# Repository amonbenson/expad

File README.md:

# expad - Expression Adapter

A four-jack USB MIDI adapter for expression and sustain pedals, built on a Raspberry Pi Pico 2 W.
It works out what is plugged into each jack - whichever contact a pedal's wiper is on, and whether
it is a potentiometer, a switch or a two-wire rheostat - and sends every pedal's position as a MIDI
control change, ~190 times per second. A WiFi access point serves a web interface for watching the
jacks and changing the settings live.

## Hardware

The PCB is the KiCad project in [hardware/](hardware/). Each jack's tip, ring and sleeve (plus the
tip's switch contact, for plug detection) can be switched to a shared 1 kΩ pull-up to the 2.5 V
reference or a 1 kΩ pull-down, and is read back by one of two AD7718 24-bit ADCs. The four
WS2812B LEDs below the jacks glow a dim white while a plug is in but no known pedal is behind it.
A recognised pedal is announced for a second in its own color - purple for an expression pedal,
lime for a footswitch, yellow for a rheostat - after which the LED shows the value it sends, from
dark red at 0 through red, orange and yellow to white at 127. They run off a linear regulator, so
the firmware caps them at ~4% brightness.

## Supported pedals

| Pedal | Cable | Shown as | Value |
|---|---|---|---|
| Expression pedal (potentiometer), wiper on tip or ring | stereo (TRS) | Tracking | wiper position, counting up away from the sleeve |
| Sustain pedal / footswitch | mono (TS) or stereo | Switch | 100% closed, 0% open |
| Two-wire (rheostat) expression pedal | mono or stereo | Rheostat | resistance against the nearest standard value (10k, 25k, 50k ...) |
| Anything else (dual footswitches, other wirings) | | Other pedal | none |

Pedals are recognised within ~0.1 s of being plugged in, and unplugging is noticed just as fast.

- A normally-closed sustain pedal, or an expression pedal wired the other way round, needs
  **Invert**.
- A rheostat pedal on a mono cable first reads as a potentiometer at rest, until its resistance has
  changed by a fifth.
- A potentiometer pedal needs a stereo cable: with a mono one, most pedals short their ring to the
  sleeve, which leaves a resistance that rises and falls again over the travel.
- A mono cable with nothing at the other end reads as a released switch.

## Using it

1. Plug the Pico into a computer over USB. It shows up as a USB MIDI device; by default the
   first two jacks send CC 11 (Expression) and the last two CC 1 (Modulation), all on MIDI
   channel 1.
2. Join the WiFi network **Expression Adapter** (password: the one it was built with, see below).
   Phones, tablets and computers open the interface by themselves as the network's sign-in page;
   otherwise open http://192.168.4.1.
3. Per jack, set the MIDI channel and controller, **Invert**, and the **Range**: move the pedal to
   one end and press **Min**, to the other and press **Max**, so its travel covers the full MIDI
   range. **Drive** bends the response against a pedal's nonlinear track: centered is linear,
   turning it right makes the value rise early in the travel, left late (double-click resets it).
   **Wiper** only matters for pedals whose wiper is on the ring or sleeve and that rest on an
   end stop when plugged in; **Auto** handles the common wirings. The LED slider sets the
   brightness.

The topology panel on the right draws the selected jack's measured network.

## Setup

Needs Rust, Node.js (see `engines` in [web/package.json](web/package.json)) for the web interface,
and a debug probe (e.g. a Raspberry Pi Debug Probe) on the Pico's SWD pins.

```bash
rustup target add thumbv8m.main-none-eabihf
cargo install probe-rs-tools --locked
cp .env.example .env   # then set EXPAD_WIFI_PASSWORD (8-63 characters)
```

## Building and flashing

```bash
cargo run --bin expression_controller   # build, flash and show the log
cargo run --bin expression_controller --features no-wifi   # the same with the radio off
cargo build --no-default-features       # without the web interface (no Node.js needed)
```

The other programs in [src/bin/](src/bin/) test parts of the board:

| Program | What it does |
|---|---|
| `detect_pin_mapping` | checks every contact's switches and ADC input against the wiring table (unplug all jacks) |
| `capture` | holds every contact in one state and logs every ADC input, for noise measurements |
| `adc_characterization` | compares ADC filter rates and SPI settings on a pedal in jack 1 |
| `potentiometer` | reads a pedal in jack 1 and shows its position on the LEDs |
| `rainbow` | LED strip test |
| `midi_loopback` | echoes every USB MIDI message back to the host |
| `web_interface` | the web interface with made-up data |

## Development

```bash
cargo test -p expad-topology --target x86_64-pc-windows-msvc   # solver tests, on your host triple
cargo fmt
cargo clippy --all-features
cd web && npm run dev:mock   # web interface against a simulated device, no hardware needed
```

[AGENTS.md](AGENTS.md) describes the repository in detail, and
[docs/fast-tracking.md](docs/fast-tracking.md) the measurements and design behind the pedal
detection.

## General TODOs
- missing standard trait implementations for all types (Debug, Default, Clone, Copy, PartialEq, Eq, etc.)
- missing with_field builder methods for all config structs
- thiserror (nostd) or similar better error handling

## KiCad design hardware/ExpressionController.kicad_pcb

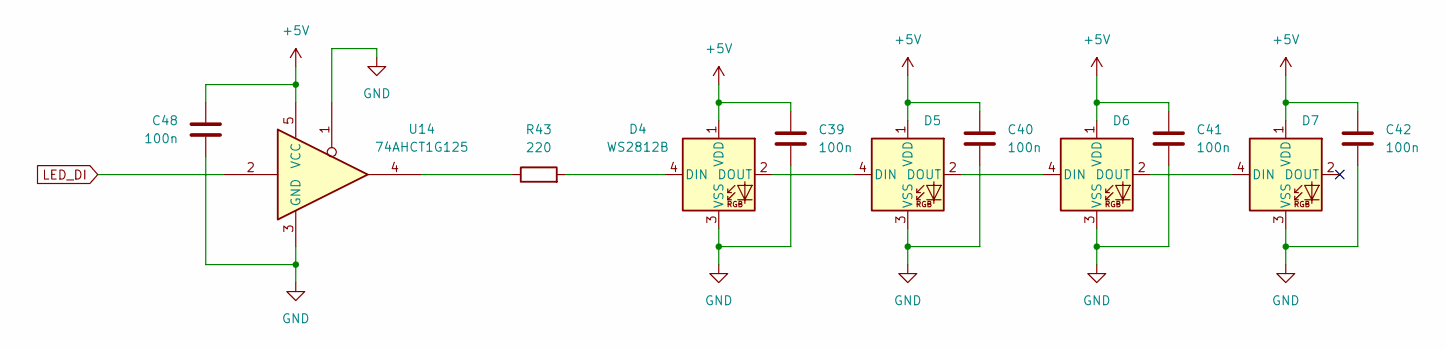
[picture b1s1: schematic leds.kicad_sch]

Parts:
C39, C40, C41, C42, C48: 100n; C_0805_2012Metric; Part Source Uni
D4, D5, D6, D7: WS2812B; LED_WS2812B_PLCC4_5.0x5.0mm_P3.2mm; Part Source Mouser; Mouser No 485-1655
R43: 220; R_0805_2012Metric; Part Source Uni
U14: 74AHCT1G125; SOT-353_SC-70-5; Part Source Mouser; Mouser No 595-74AHCT1G125DCKRG

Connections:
+5V: C39.1, C40.1, C41.1, C42.1, C48.1, D4.1 (VDD), D5.1 (VDD), D6.1 (VDD), D7.1 (VDD), U14.5 (VCC); also elsewhere on the board
GND: C39.2, C40.2, C41.2, C42.2, C48.2, D4.3 (VSS), D5.3 (VSS), D6.3 (VSS), D7.3 (VSS), U14.1, U14.3 (GND); also elsewhere on the board
LED_DI: U14.2; also elsewhere on the board
unnamed: D4.4 (DIN), R43.2
unnamed: D4.2 (DOUT), D5.4 (DIN)
unnamed: D5.2 (DOUT), D6.4 (DIN)
unnamed: D6.2 (DOUT), D7.4 (DIN)
unnamed: R43.1, U14.4

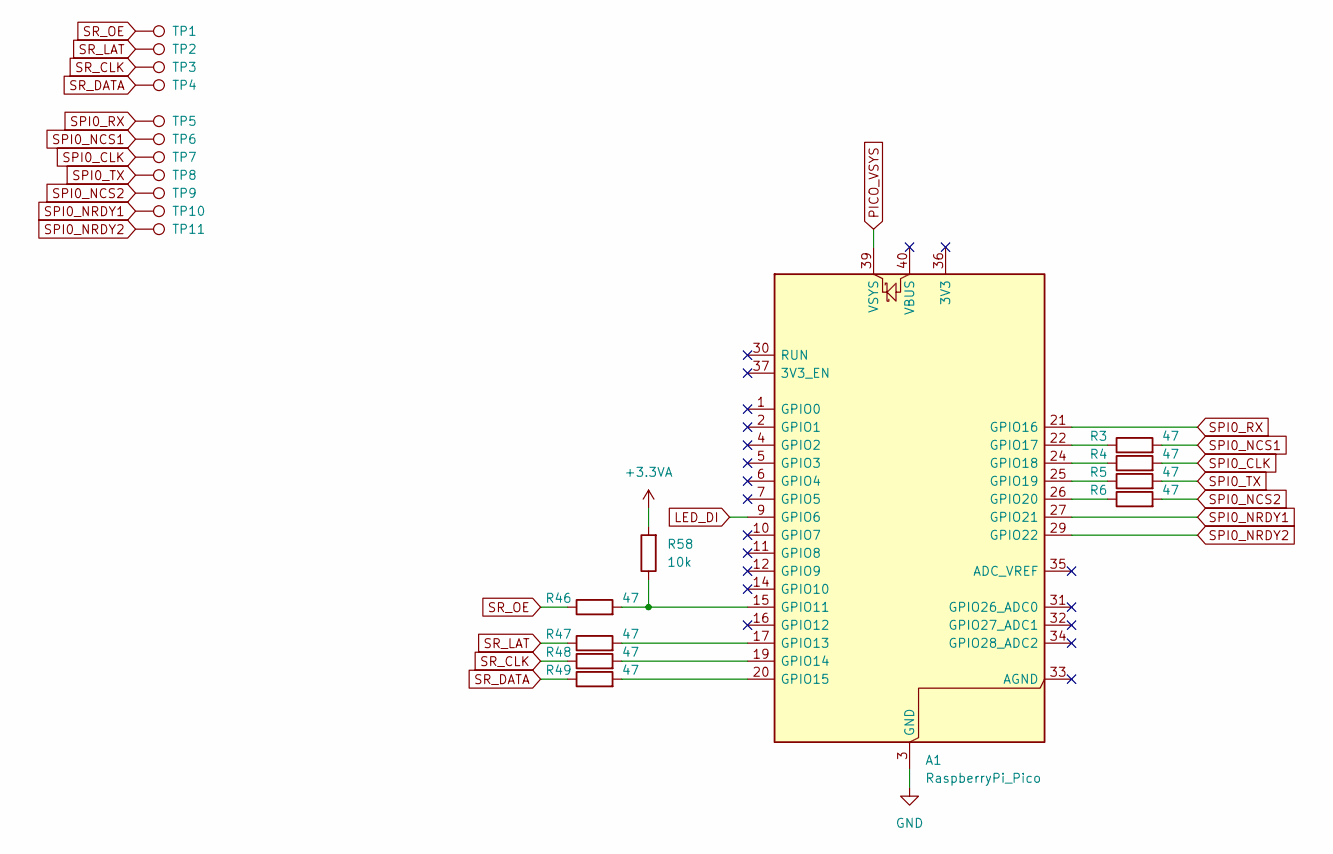
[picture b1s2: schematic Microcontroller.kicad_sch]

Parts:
A1: RaspberryPi_Pico; Pico_2W_with_Header; Part Source Uni
R3, R4, R5, R6, R46, R47, R48, R49: 47; R_0805_2012Metric; Part Source Uni
R58: 10k; R_0805_2012Metric; Part Source Uni
TP1, TP2, TP3, TP4, TP5, TP6, TP7, TP8, TP9, TP10, TP11: TestPoint; TestPoint_THTPad_D1.5mm_Drill0.7mm

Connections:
+3.3VA: R58.2; also elsewhere on the board
GND: A1.3 (GND), A1.8 (GND), A1.13 (GND), A1.18 (GND), A1.23 (GND), A1.28 (GND), A1.38 (GND); also elsewhere on the board
LED_DI: A1.9 (GPIO6); also elsewhere on the board
unnamed: A1.15 (GPIO11), R46.2, R58.1
unnamed: A1.17 (GPIO13), R47.2
unnamed: A1.19 (GPIO14), R48.2
unnamed: A1.20 (GPIO15), R49.2
unnamed: A1.22 (GPIO17), R3.1
unnamed: A1.24 (GPIO18), R4.1
unnamed: A1.25 (GPIO19), R5.1
unnamed: A1.26 (GPIO20), R6.1
PICO_VSYS: A1.39 (VSYS); also elsewhere on the board
SPI0_CLK: R4.2, TP7.1 (1_1); also elsewhere on the board
SPI0_NCS1: R3.2, TP6.1 (1_1); also elsewhere on the board
SPI0_NCS2: R6.2, TP9.1 (1_1); also elsewhere on the board
SPI0_NRDY1: A1.27 (GPIO21), TP10.1 (1_1); also elsewhere on the board
SPI0_NRDY2: A1.29 (GPIO22), TP11.1 (1_1); also elsewhere on the board
SPI0_RX: A1.21 (GPIO16), TP5.1 (1_1); also elsewhere on the board
SPI0_TX: R5.2, TP8.1 (1_1); also elsewhere on the board
SR_CLK: R48.1, TP3.1 (1_1); also elsewhere on the board
SR_DATA: R49.1, TP4.1 (1_1); also elsewhere on the board
SR_LAT: R47.1, TP2.1 (1_1); also elsewhere on the board
SR_OE: R46.1, TP1.1 (1_1); also elsewhere on the board

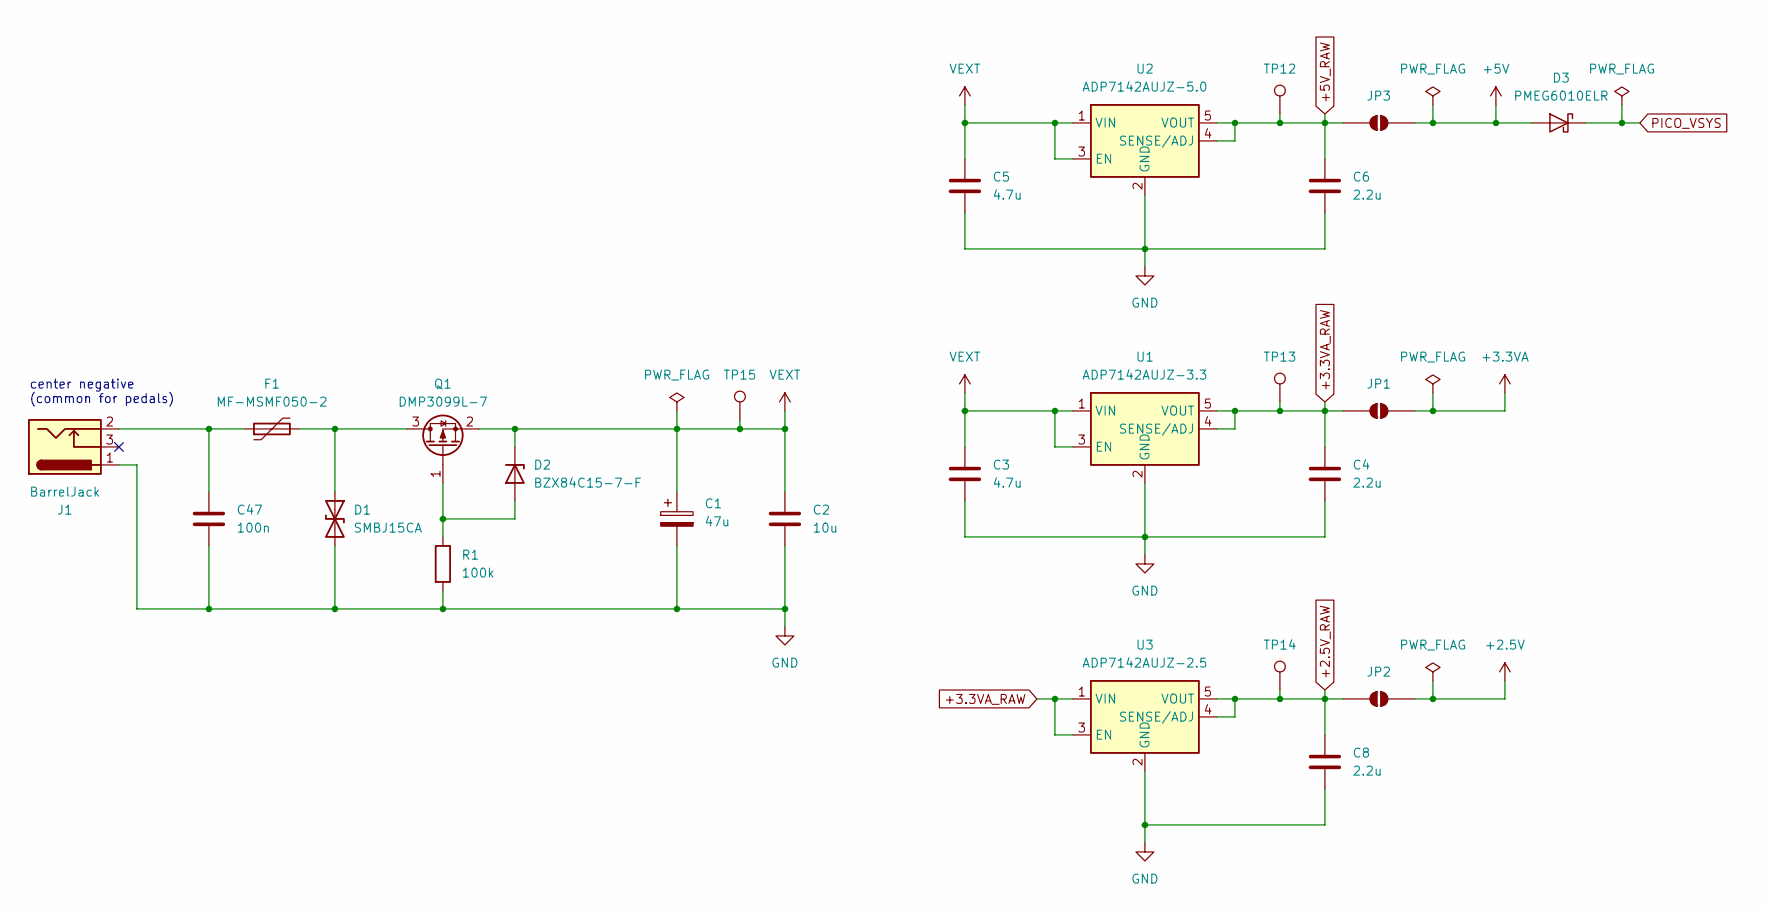
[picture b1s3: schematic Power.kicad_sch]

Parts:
C1: 47u; CP_Elec_6.3x5.8; Part Source Mouser; Mouser No 667-EEH-ZC1E470P
C2: 10u; C_0805_2012Metric; Part Source Uni
C3, C5: 4.7u; C_0805_2012Metric; Part Source Uni
C4, C6, C8: 2.2u; C_0805_2012Metric; Part Source Uni
C47: 100n; C_0805_2012Metric; Part Source Uni
D1: SMBJ15CA; D_SMB; Part Source Mouser; Mouser No 947-SMBJ15CA
D2: BZX84C15-7-F; SOT-23; Part Source Mouser; Mouser No 621-BZX84C15-F
D3: PMEG6010ELR; Nexperia_CFP3_SOD-123W; Part Source Mouser; Mouser No 771-PMEG6010ELRX
F1: MF-MSMF050-2; Fuse_1812_4532Metric; Part Source Mouser; Mouser No 652-MF-MSMF050-2
J1: BarrelJack; BarrelJack_CUI_PJ-102AH_Horizontal; Part Source Mouser; Mouser No 490-PJ-102AH
JP1, JP2, JP3: SolderJumper_2_Open; SolderJumper-2_P1.3mm_Open_RoundedPad1.0x1.5mm
Q1: DMP3099L-7; SOT-23; Part Source Mouser; Mouser No 621-DMP3099L-7
R1: 100k; R_0805_2012Metric; Part Source Uni
TP12, TP13, TP14, TP15: TestPoint; TestPoint_THTPad_D1.5mm_Drill0.7mm
U1: ADP7142AUJZ-3.3; TSOT-23-5; Part Source Mouser; Mouser No 584-ADP7142AUJZ3.3R7
U2: ADP7142AUJZ-5.0; TSOT-23-5; Part Source Mouser; Mouser No 584-ADP7142WAUJZ-50R
U3: ADP7142AUJZ-2.5; TSOT-23-5; Part Source Mouser; Mouser No 584-ADP7142AUJZ2.5R7

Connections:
+2.5V: JP2.2 (B); also elsewhere on the board
+2.5V_RAW: C8.1, JP2.1 (A), TP14.1 (1_1), U3.4 (SENSE/ADJ), U3.5 (VOUT)
+3.3VA: JP1.2 (B); also elsewhere on the board
+3.3VA_RAW: C4.1, JP1.1 (A), TP13.1 (1_1), U1.4 (SENSE/ADJ), U1.5 (VOUT), U3.1 (VIN), U3.3 (EN)
+5V: D3.2 (A), JP3.2 (B); also elsewhere on the board
+5V_RAW: C6.1, JP3.1 (A), TP12.1 (1_1), U2.4 (SENSE/ADJ), U2.5 (VOUT)
GND: C1.2, C2.2, C3.2, C4.2, C5.2, C6.2, C8.2, C47.2, D1.2 (A2), J1.1, R1.2, U1.2 (GND), U2.2 (GND), U3.2 (GND); also elsewhere on the board
unnamed: C47.1, F1.1, J1.2
unnamed: D1.1 (A1), F1.2, Q1.3 (D)
unnamed: D2.1 (A), Q1.1 (G), R1.1
PICO_VSYS: D3.1 (K); also elsewhere on the board
VEXT: C1.1, C2.1, C3.1, C5.1, D2.3 (K), Q1.2 (S), TP15.1 (1_1), U1.1 (VIN), U1.3 (EN), U2.1 (VIN), U2.3 (EN)

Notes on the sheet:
center negative (common for pedals)

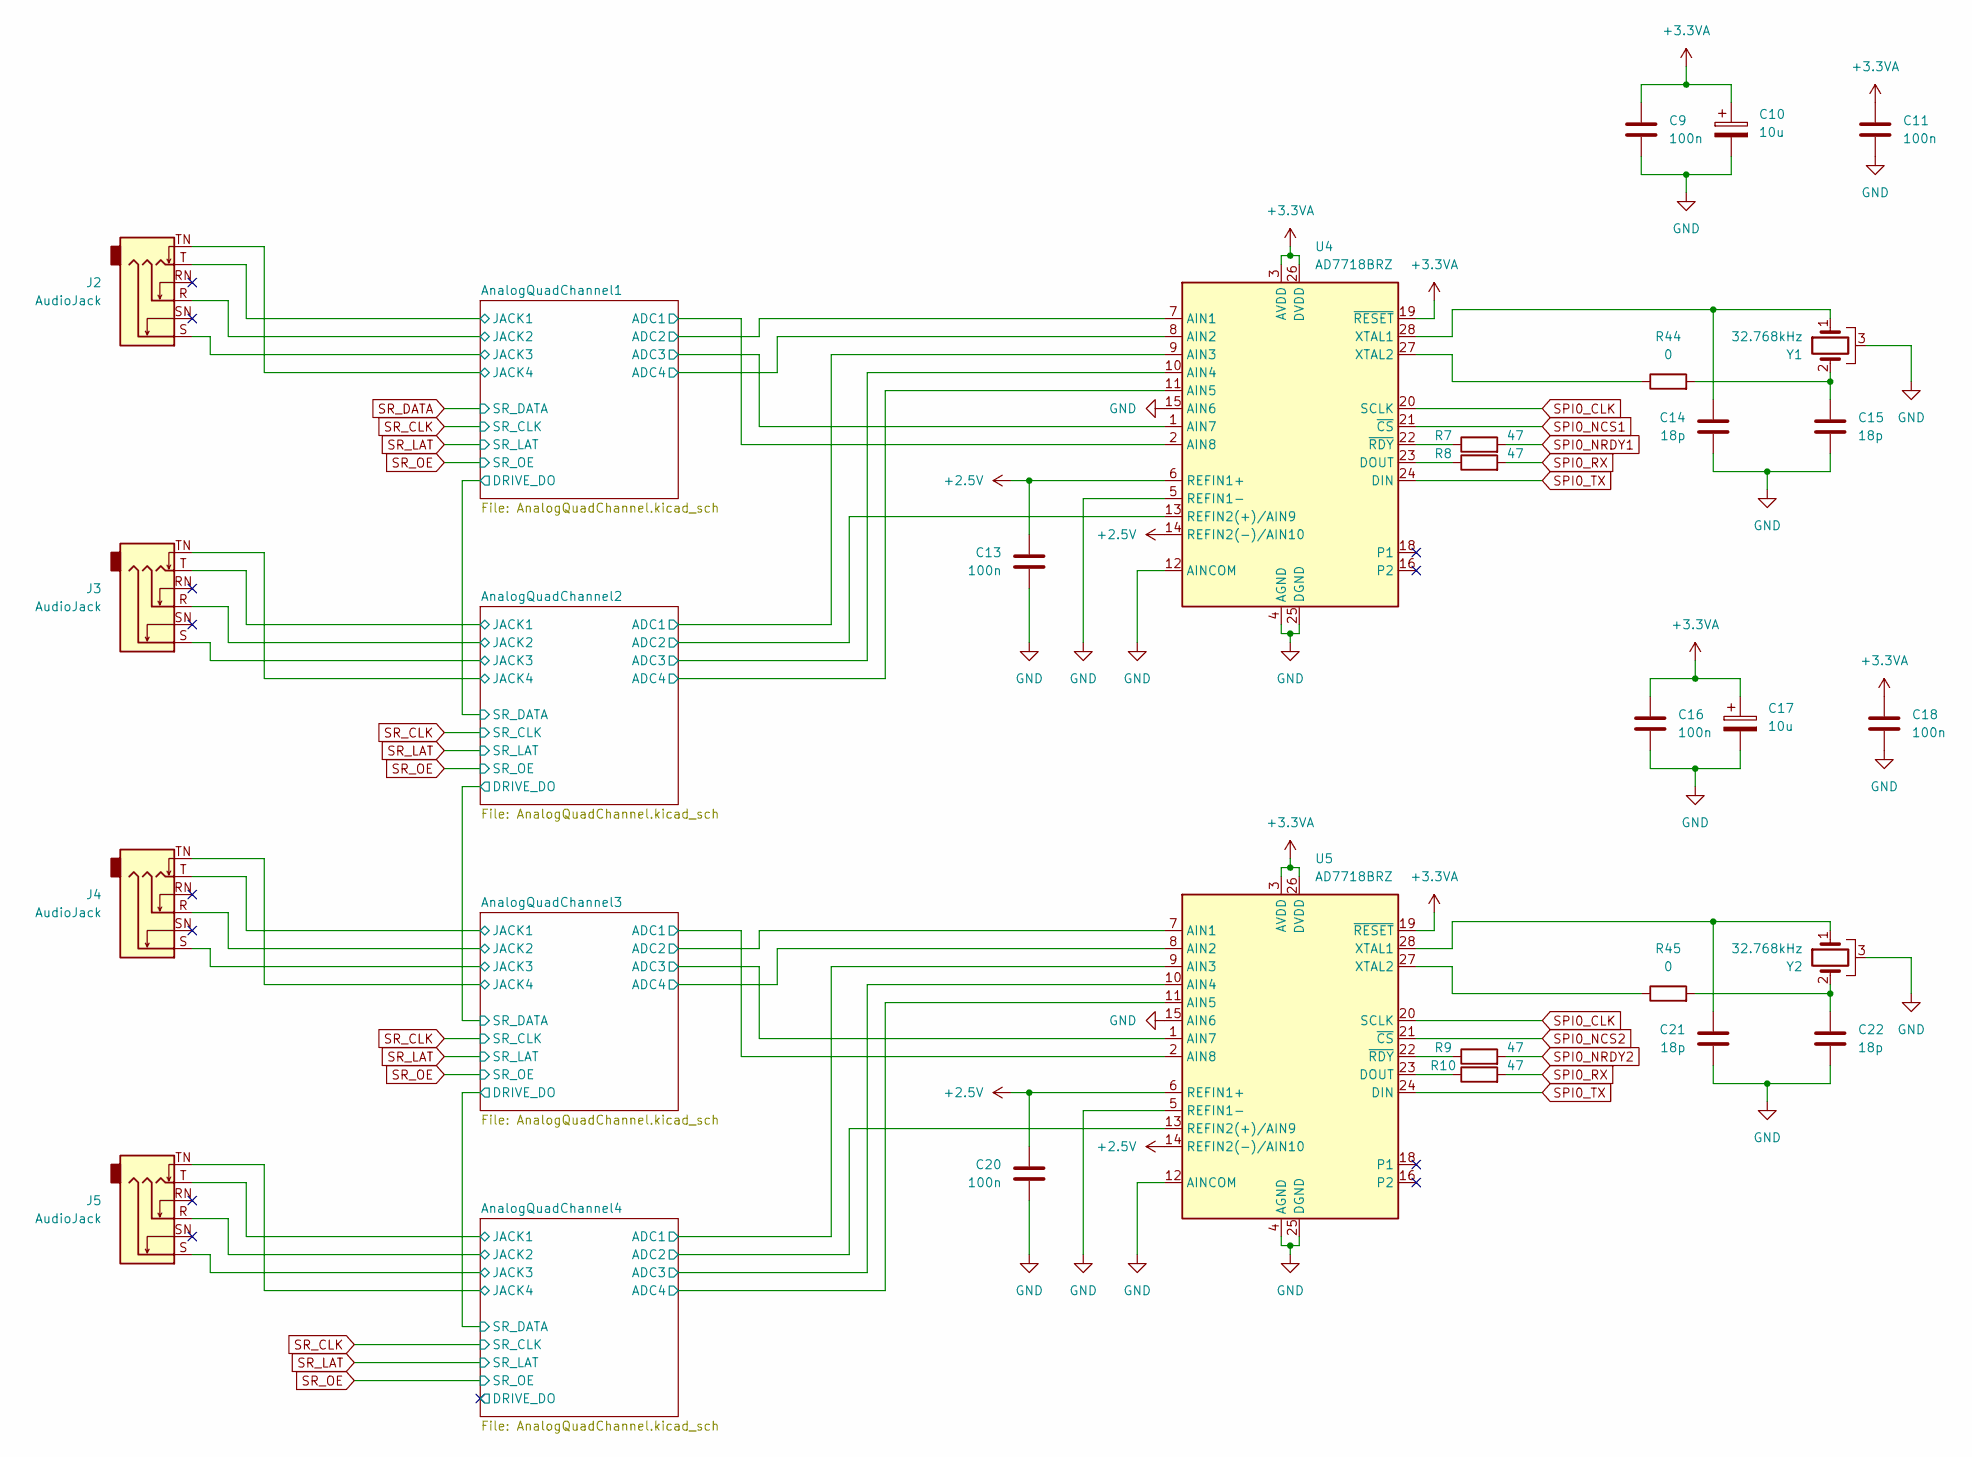
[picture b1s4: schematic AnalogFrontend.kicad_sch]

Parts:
C9, C11, C13, C16, C18, C20: 100n; C_0805_2012Metric; Part Source Uni
C10, C17: 10u; C_0805_2012Metric; Part Source Uni
C14, C15, C21, C22: 18p; C_0805_2012Metric; Part Source Uni
J2, J3, J4, J5: AudioJack; Jack_6.35mm_Neutrik_NMJ6HFD4_Horizontal; Part Source Mouser; Mouser No 568-NMJ6HFD2-AU
R7, R8, R9, R10: 47; R_0805_2012Metric; Part Source Uni
R44, R45: 0; R_0805_2012Metric; Part Source Uni
U4, U5: AD7718BRZ; SOIC-28W_7.5x17.9mm_P1.27mm; Part Source Mouser; Mouser No 584-AD7718BRZ
Y1, Y2: 32.768kHz; MS1V-T1K; Part Source Mouser; Mouser No 428-200120-ML02

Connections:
+2.5V: C13.1, C20.1, U4.6 (REFIN1+), U4.14 (REFIN2(-)/AIN10), U5.6 (REFIN1+), U5.14 (REFIN2(-)/AIN10); also elsewhere on the board
+3.3VA: C9.1, C10.1, C11.1, C16.1, C17.1, C18.1, U4.3 (AVDD), U4.19 (~RESET), U4.26 (DVDD), U5.3 (AVDD), U5.19 (~RESET), U5.26 (DVDD); also elsewhere on the board
/AnalogFrontend/AnalogQuadChannel1/ADC1: U4.2 (AIN8); also elsewhere on the board
/AnalogFrontend/AnalogQuadChannel1/ADC2: U4.7 (AIN1); also elsewhere on the board
/AnalogFrontend/AnalogQuadChannel1/ADC3: U4.1 (AIN7); also elsewhere on the board
/AnalogFrontend/AnalogQuadChannel1/ADC4: U4.8 (AIN2); also elsewhere on the board
/AnalogFrontend/AnalogQuadChannel1/JACK1: J2.T; also elsewhere on the board
/AnalogFrontend/AnalogQuadChannel1/JACK2: J2.R; also elsewhere on the board
/AnalogFrontend/AnalogQuadChannel1/JACK3: J2.S; also elsewhere on the board
/AnalogFrontend/AnalogQuadChannel1/JACK4: J2.TN; also elsewhere on the board
/AnalogFrontend/AnalogQuadChannel2/ADC1: U4.9 (AIN3); also elsewhere on the board
/AnalogFrontend/AnalogQuadChannel2/ADC2: U4.13 (REFIN2(+)/AIN9); also elsewhere on the board
/AnalogFrontend/AnalogQuadChannel2/ADC3: U4.10 (AIN4); also elsewhere on the board
/AnalogFrontend/AnalogQuadChannel2/ADC4: U4.11 (AIN5); also elsewhere on the board
/AnalogFrontend/AnalogQuadChannel2/JACK1: J3.T; also elsewhere on the board
/AnalogFrontend/AnalogQuadChannel2/JACK2: J3.R; also elsewhere on the board
/AnalogFrontend/AnalogQuadChannel2/JACK3: J3.S; also elsewhere on the board
/AnalogFrontend/AnalogQuadChannel2/JACK4: J3.TN; also elsewhere on the board
/AnalogFrontend/AnalogQuadChannel3/ADC1: U5.2 (AIN8); also elsewhere on the board
/AnalogFrontend/AnalogQuadChannel3/ADC2: U5.7 (AIN1); also elsewhere on the board
/AnalogFrontend/AnalogQuadChannel3/ADC3: U5.1 (AIN7); also elsewhere on the board
/AnalogFrontend/AnalogQuadChannel3/ADC4: U5.8 (AIN2); also elsewhere on the board
/AnalogFrontend/AnalogQuadChannel3/JACK1: J4.T; also elsewhere on the board
/AnalogFrontend/AnalogQuadChannel3/JACK2: J4.R; also elsewhere on the board
/AnalogFrontend/AnalogQuadChannel3/JACK3: J4.S; also elsewhere on the board
/AnalogFrontend/AnalogQuadChannel3/JACK4: J4.TN; also elsewhere on the board
/AnalogFrontend/AnalogQuadChannel4/ADC1: U5.9 (AIN3); also elsewhere on the board
/AnalogFrontend/AnalogQuadChannel4/ADC2: U5.13 (REFIN2(+)/AIN9); also elsewhere on the board
/AnalogFrontend/AnalogQuadChannel4/ADC3: U5.10 (AIN4); also elsewhere on the board
/AnalogFrontend/AnalogQuadChannel4/ADC4: U5.11 (AIN5); also elsewhere on the board
/AnalogFrontend/AnalogQuadChannel4/JACK1: J5.T; also elsewhere on the board
/AnalogFrontend/AnalogQuadChannel4/JACK2: J5.R; also elsewhere on the board
/AnalogFrontend/AnalogQuadChannel4/JACK3: J5.S; also elsewhere on the board
/AnalogFrontend/AnalogQuadChannel4/JACK4: J5.TN; also elsewhere on the board
GND: C9.2, C10.2, C11.2, C13.2, C14.2, C15.2, C16.2, C17.2, C18.2, C20.2, C21.2, C22.2, U4.4 (AGND), U4.5 (REFIN1-), U4.12 (AINCOM), U4.15 (AIN6), U4.17 (AGND), U4.25 (DGND), U5.4 (AGND), U5.5 (REFIN1-), U5.12 (AINCOM), U5.15 (AIN6), U5.17 (AGND), U5.25 (DGND), Y1.3, Y2.3; also elsewhere on the board
unnamed: C15.1, R44.2, Y1.2
unnamed: C22.1, R45.2, Y2.2
unnamed: R8.1, U4.23 (DOUT)
unnamed: C14.1, U4.28 (XTAL1), Y1.1
unnamed: R44.1, U4.27 (XTAL2)
unnamed: R7.1, U4.22 (~RDY)
unnamed: R10.1, U5.23 (DOUT)
unnamed: C21.1, U5.28 (XTAL1), Y2.1
unnamed: R45.1, U5.27 (XTAL2)
unnamed: R9.1, U5.22 (~RDY)
SPI0_CLK: U4.20 (SCLK), U5.20 (SCLK); also elsewhere on the board
SPI0_NCS1: U4.21 (~CS); also elsewhere on the board
SPI0_NCS2: U5.21 (~CS); also elsewhere on the board
SPI0_NRDY1: R7.2; also elsewhere on the board
SPI0_NRDY2: R9.2; also elsewhere on the board
SPI0_RX: R8.2, R10.2; also elsewhere on the board
SPI0_TX: U4.24 (DIN), U5.24 (DIN); also elsewhere on the board

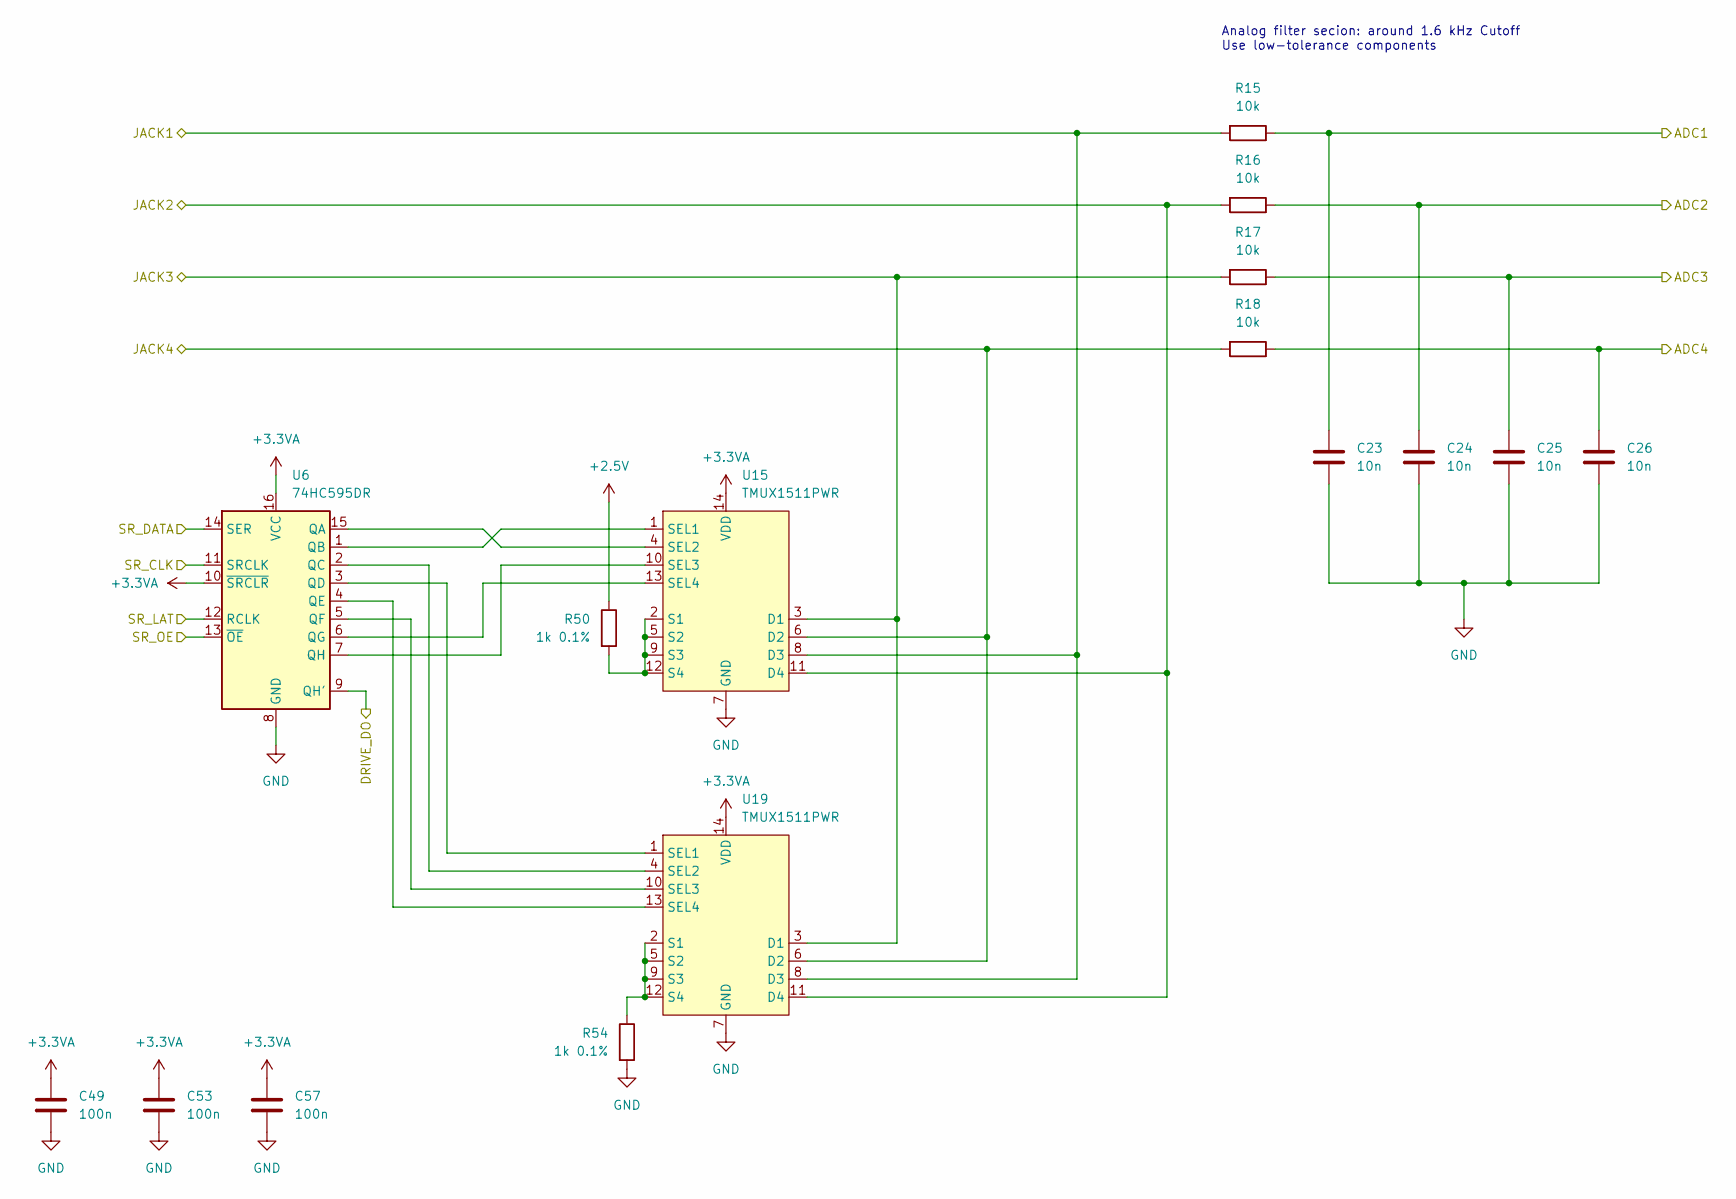
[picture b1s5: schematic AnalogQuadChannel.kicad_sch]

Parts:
C23, C24, C25, C26: 10n; C_0805_2012Metric; Part Source Uni
C49, C53, C57: 100n; C_0805_2012Metric; Part Source Uni
R15, R16, R17, R18: 10k; R_0805_2012Metric; Part Source Uni
R50, R54: 1k 0.1%; R_0805_2012Metric; Part Source Mouser; Mouser No ERA-6AEB102V
U6: 74HC595DR; SOIC-16_3.9x9.9mm_P1.27mm; Part Source Mouser; Mouser No 595-SN74HC595DR
U15, U19: TMUX1511PWR; TSSOP-14_4.4x5mm_P0.65mm; Part Source Mouser; Mouser No 595-TMUX1511PWR

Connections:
+2.5V: R50.1; also elsewhere on the board
+3.3VA: C49.1, C53.1, C57.1, U6.10 (~SRCLR), U6.16 (VCC), U15.14 (VDD), U19.14 (VDD); also elsewhere on the board
/AnalogFrontend/AnalogQuadChannel1/ADC1: C23.1, R15.1; also elsewhere on the board
/AnalogFrontend/AnalogQuadChannel1/ADC2: C24.1, R16.1; also elsewhere on the board
/AnalogFrontend/AnalogQuadChannel1/ADC3: C25.1, R17.1; also elsewhere on the board
/AnalogFrontend/AnalogQuadChannel1/ADC4: C26.1, R18.1; also elsewhere on the board
/AnalogFrontend/AnalogQuadChannel1/DRIVE_DO: U6.9 (QH'); also elsewhere on the board
/AnalogFrontend/AnalogQuadChannel1/JACK1: R15.2, U15.8 (D3), U19.8 (D3); also elsewhere on the board
/AnalogFrontend/AnalogQuadChannel1/JACK2: R16.2, U15.11 (D4), U19.11 (D4); also elsewhere on the board
/AnalogFrontend/AnalogQuadChannel1/JACK3: R17.2, U15.3 (D1), U19.3 (D1); also elsewhere on the board
/AnalogFrontend/AnalogQuadChannel1/JACK4: R18.2, U15.6 (D2), U19.6 (D2); also elsewhere on the board
GND: C23.2, C24.2, C25.2, C26.2, C49.2, C53.2, C57.2, R54.2, U6.8 (GND), U15.7 (GND), U19.7 (GND); also elsewhere on the board
unnamed: R50.2, U15.2 (S1), U15.5 (S2), U15.9 (S3), U15.12 (S4)
unnamed: U6.1 (QB), U15.1 (SEL1)
unnamed: U6.15 (QA), U15.4 (SEL2)
unnamed: U6.7 (QH), U15.10 (SEL3)
unnamed: U6.6 (QG), U15.13 (SEL4)
unnamed: R54.1, U19.2 (S1), U19.5 (S2), U19.9 (S3), U19.12 (S4)
unnamed: U6.3 (QD), U19.1 (SEL1)
unnamed: U6.2 (QC), U19.4 (SEL2)
unnamed: U6.5 (QF), U19.10 (SEL3)
unnamed: U6.4 (QE), U19.13 (SEL4)
SR_CLK: U6.11 (SRCLK); also elsewhere on the board
SR_DATA: U6.14 (SER); also elsewhere on the board
SR_LAT: U6.12 (RCLK); also elsewhere on the board
SR_OE: U6.13 (~OE); also elsewhere on the board

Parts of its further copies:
C27, C28, C29, C30, C31, C32, C33, C34, C35, C36, C37, C38: 10n; C_0805_2012Metric; Part Source Uni
C50, C51, C52, C54, C55, C56, C58, C59, C60: 100n; C_0805_2012Metric; Part Source Uni
R23, R24, R25, R26, R31, R32, R33, R34, R39, R40, R41, R42: 10k; R_0805_2012Metric; Part Source Uni
R51, R52, R53, R55, R56, R57: 1k 0.1%; R_0805_2012Metric; Part Source Mouser; Mouser No ERA-6AEB102V
U8, U10, U12: 74HC595DR; SOIC-16_3.9x9.9mm_P1.27mm; Part Source Mouser; Mouser No 595-SN74HC595DR
U16, U17, U18, U20, U21, U22: TMUX1511PWR; TSSOP-14_4.4x5mm_P0.65mm; Part Source Mouser; Mouser No 595-TMUX1511PWR

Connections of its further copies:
+2.5V: R51.1, R52.1, R53.1; also elsewhere on the board
+3.3VA: C50.1, C51.1, C52.1, C54.1, C55.1, C56.1, C58.1, C59.1, C60.1, U8.10 (~SRCLR), U8.16 (VCC), U10.10 (~SRCLR), U10.16 (VCC), U12.10 (~SRCLR), U12.16 (VCC), U16.14 (VDD), U17.14 (VDD), U18.14 (VDD), U20.14 (VDD), U21.14 (VDD), U22.14 (VDD); also elsewhere on the board
/AnalogFrontend/AnalogQuadChannel1/DRIVE_DO: U8.14 (SER); also elsewhere on the board
/AnalogFrontend/AnalogQuadChannel2/ADC1: C27.1, R23.1; also elsewhere on the board
/AnalogFrontend/AnalogQuadChannel2/ADC2: C28.1, R24.1; also elsewhere on the board
/AnalogFrontend/AnalogQuadChannel2/ADC3: C29.1, R25.1; also elsewhere on the board
/AnalogFrontend/AnalogQuadChannel2/ADC4: C30.1, R26.1; also elsewhere on the board
/AnalogFrontend/AnalogQuadChannel2/DRIVE_DO: U8.9 (QH'), U10.14 (SER)
/AnalogFrontend/AnalogQuadChannel2/JACK1: R23.2, U16.8 (D3), U20.8 (D3); also elsewhere on the board
/AnalogFrontend/AnalogQuadChannel2/JACK2: R24.2, U16.11 (D4), U20.11 (D4); also elsewhere on the board
/AnalogFrontend/AnalogQuadChannel2/JACK3: R25.2, U16.3 (D1), U20.3 (D1); also elsewhere on the board
/AnalogFrontend/AnalogQuadChannel2/JACK4: R26.2, U16.6 (D2), U20.6 (D2); also elsewhere on the board
/AnalogFrontend/AnalogQuadChannel3/ADC1: C31.1, R31.1; also elsewhere on the board
/AnalogFrontend/AnalogQuadChannel3/ADC2: C32.1, R32.1; also elsewhere on the board
/AnalogFrontend/AnalogQuadChannel3/ADC3: C33.1, R33.1; also elsewhere on the board
/AnalogFrontend/AnalogQuadChannel3/ADC4: C34.1, R34.1; also elsewhere on the board
/AnalogFrontend/AnalogQuadChannel3/DRIVE_DO: U10.9 (QH'), U12.14 (SER)
/AnalogFrontend/AnalogQuadChannel3/JACK1: R31.2, U17.8 (D3), U21.8 (D3); also elsewhere on the board
/AnalogFrontend/AnalogQuadChannel3/JACK2: R32.2, U17.11 (D4), U21.11 (D4); also elsewhere on the board
/AnalogFrontend/AnalogQuadChannel3/JACK3: R33.2, U17.3 (D1), U21.3 (D1); also elsewhere on the board
/AnalogFrontend/AnalogQuadChannel3/JACK4: R34.2, U17.6 (D2), U21.6 (D2); also elsewhere on the board
/AnalogFrontend/AnalogQuadChannel4/ADC1: C35.1, R39.1; also elsewhere on the board
/AnalogFrontend/AnalogQuadChannel4/ADC2: C36.1, R40.1; also elsewhere on the board
/AnalogFrontend/AnalogQuadChannel4/ADC3: C37.1, R41.1; also elsewhere on the board
/AnalogFrontend/AnalogQuadChannel4/ADC4: C38.1, R42.1; also elsewhere on the board
/AnalogFrontend/AnalogQuadChannel4/DRIVE_DO: U12.9 (QH')
/AnalogFrontend/AnalogQuadChannel4/JACK1: R39.2, U18.8 (D3), U22.8 (D3); also elsewhere on the board
/AnalogFrontend/AnalogQuadChannel4/JACK2: R40.2, U18.11 (D4), U22.11 (D4); also elsewhere on the board
/AnalogFrontend/AnalogQuadChannel4/JACK3: R41.2, U18.3 (D1), U22.3 (D1); also elsewhere on the board
/AnalogFrontend/AnalogQuadChannel4/JACK4: R42.2, U18.6 (D2), U22.6 (D2); also elsewhere on the board
GND: C27.2, C28.2, C29.2, C30.2, C31.2, C32.2, C33.2, C34.2, C35.2, C36.2, C37.2, C38.2, C50.2, C51.2, C52.2, C54.2, C55.2, C56.2, C58.2, C59.2, C60.2, R55.2, R56.2, R57.2, U8.8 (GND), U10.8 (GND), U12.8 (GND), U16.7 (GND), U17.7 (GND), U18.7 (GND), U20.7 (GND), U21.7 (GND), U22.7 (GND); also elsewhere on the board
unnamed: U10.15 (QA), U17.4 (SEL2)
unnamed: U10.1 (QB), U17.1 (SEL1)
unnamed: U10.2 (QC), U21.4 (SEL2)
unnamed: U10.3 (QD), U21.1 (SEL1)
unnamed: U10.4 (QE), U21.13 (SEL4)
unnamed: U10.5 (QF), U21.10 (SEL3)
unnamed: U10.6 (QG), U17.13 (SEL4)
unnamed: U10.7 (QH), U17.10 (SEL3)
unnamed: U12.15 (QA), U18.4 (SEL2)
unnamed: U12.1 (QB), U18.1 (SEL1)
unnamed: U12.2 (QC), U22.4 (SEL2)
unnamed: U12.3 (QD), U22.1 (SEL1)
unnamed: U12.4 (QE), U22.13 (SEL4)
unnamed: U12.5 (QF), U22.10 (SEL3)
unnamed: U12.6 (QG), U18.13 (SEL4)
unnamed: U12.7 (QH), U18.10 (SEL3)
unnamed: R51.2, U16.2 (S1), U16.5 (S2), U16.9 (S3), U16.12 (S4)
unnamed: U8.1 (QB), U16.1 (SEL1)
unnamed: U8.15 (QA), U16.4 (SEL2)
unnamed: U8.7 (QH), U16.10 (SEL3)
unnamed: U8.6 (QG), U16.13 (SEL4)
unnamed: R52.2, U17.2 (S1), U17.5 (S2), U17.9 (S3), U17.12 (S4)
unnamed: R53.2, U18.2 (S1), U18.5 (S2), U18.9 (S3), U18.12 (S4)
unnamed: R55.1, U20.2 (S1), U20.5 (S2), U20.9 (S3), U20.12 (S4)
unnamed: U8.3 (QD), U20.1 (SEL1)
unnamed: U8.2 (QC), U20.4 (SEL2)
unnamed: U8.5 (QF), U20.10 (SEL3)
unnamed: U8.4 (QE), U20.13 (SEL4)
unnamed: R56.1, U21.2 (S1), U21.5 (S2), U21.9 (S3), U21.12 (S4)
unnamed: R57.1, U22.2 (S1), U22.5 (S2), U22.9 (S3), U22.12 (S4)
SR_CLK: U8.11 (SRCLK), U10.11 (SRCLK), U12.11 (SRCLK); also elsewhere on the board
SR_LAT: U8.12 (RCLK), U10.12 (RCLK), U12.12 (RCLK); also elsewhere on the board
SR_OE: U8.13 (~OE), U10.13 (~OE), U12.13 (~OE); also elsewhere on the board

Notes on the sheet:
Analog filter secion: around 1.6 kHz Cutoff Use low-tolerance components

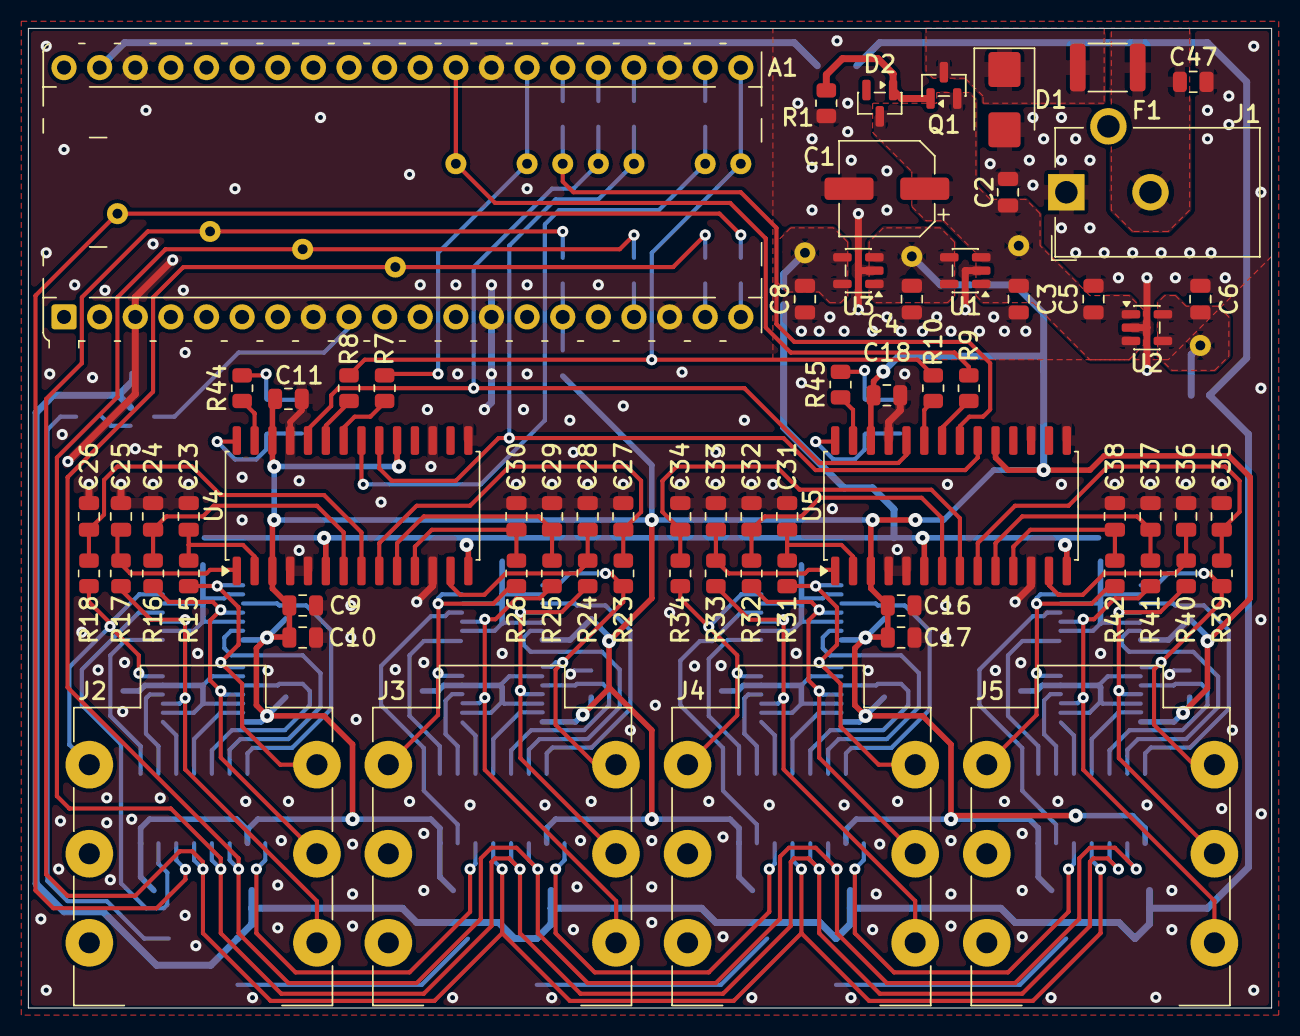
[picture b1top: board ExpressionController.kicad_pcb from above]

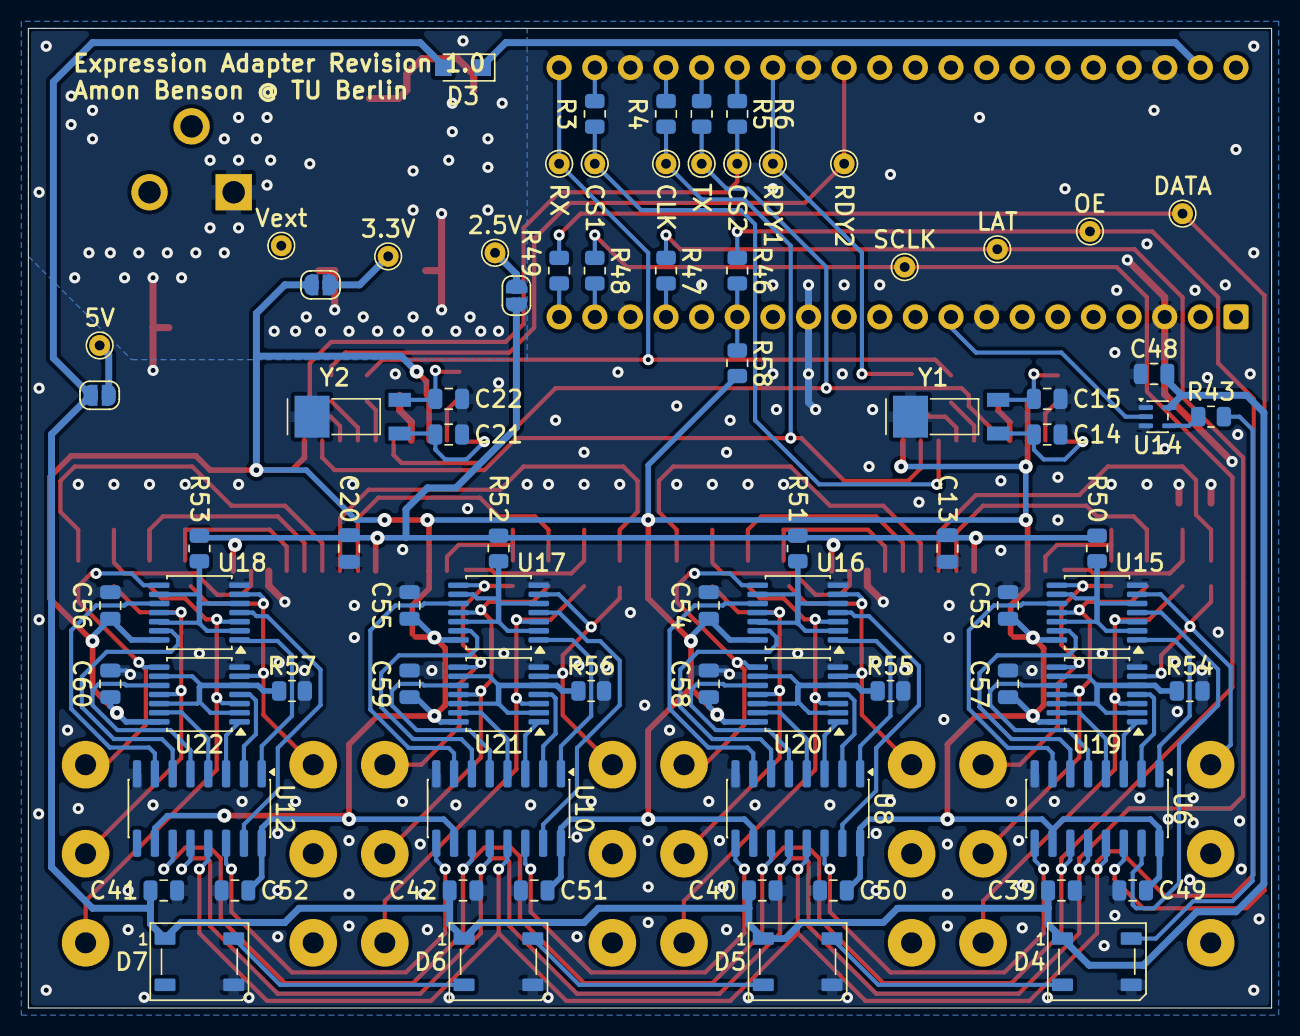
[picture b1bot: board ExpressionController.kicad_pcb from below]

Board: 2 copper layers, 88.6 x 69.8 mm, 147 parts (79 on the bottom side), 122 nets.
